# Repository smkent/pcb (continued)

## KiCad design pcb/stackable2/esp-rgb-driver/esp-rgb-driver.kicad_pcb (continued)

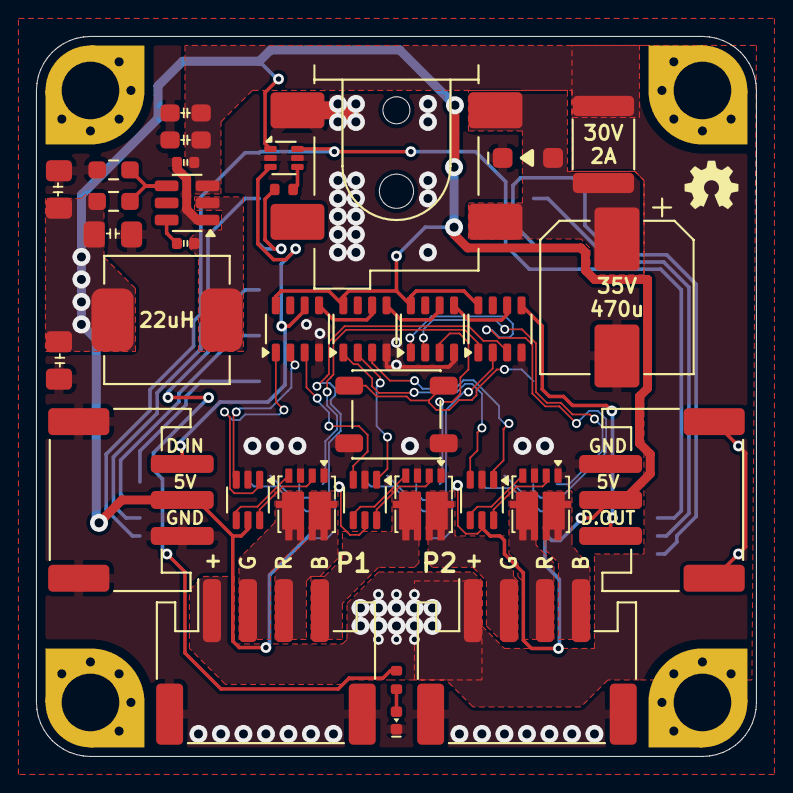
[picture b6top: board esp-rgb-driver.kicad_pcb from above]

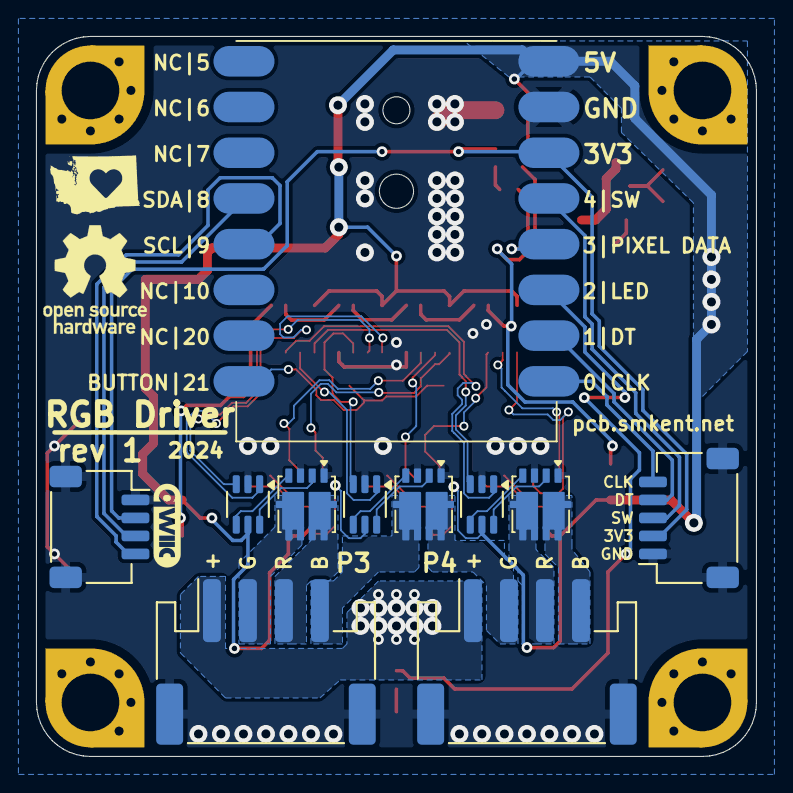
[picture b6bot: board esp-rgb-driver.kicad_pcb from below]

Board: 2 copper layers, 40.0 x 40.0 mm, 45 parts (11 on the bottom side), 59 nets.

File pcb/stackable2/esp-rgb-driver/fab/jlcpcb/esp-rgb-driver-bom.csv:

Comment,Designator,Footprint,LCSC
JST PH,"J1,J2,J3,J4",connectors:JST_PH_S4B-PH-SM4-TB_1x04-1MP_P2.00mm_Horizontal,
LED,LED1,led:LED_0402_1005Metric,
30V 2A,F1,Fuse:Fuse_1812_4532Metric,
22u,"C5,C6,C7",custom:C_0805_2012Metric_Pad1.18x1.45mm_HandSolder,
ZC010DNG,"Q1,Q2,Q3,Q4,Q5,Q6",packages:PDFN-8_L3.2-W3.1-P0.65-LS3.4-BL-EP2,C36499170
100K,R1,Resistor_SMD:R_0603_1608Metric_Pad0.98x0.95mm_HandSolder,
WS2811F,"U3,U4,U5,U6",packages:FSOP-8_L3.3-W1.7-P0.80-LS2.9-BL,C5446692
NC7WZ14,"U7,U8,U9,U10,U11,U12",packages:SOT-363_SC-70-6_HandSolder,
0u1,"C3,C4",passives:C_0402_1005Metric,
13K3,R2,Resistor_SMD:R_0603_1608Metric_Pad0.98x0.95mm_HandSolder,
~,SM1,modules:ESP32-C3-Super-Mini-Castellated-SMD-only,
Qwiic,J8,connectors:Qwiic-SMD-horizontal-logo,
TPS54202DDCR,U1,Package_TO_SOT_SMD:SOT-23-6,C191884
470u,C0,Capacitor_SMD:CP_Elec_8x10,
D_TVS,D1,packages:D_SOD-123F,
10K,R4,passives:R_0402_1005Metric,
JST SH,J7,connectors:JST_SH_SM05B-SRSS-TB_1x05-1MP_P1.00mm_Horizontal,
SN74LVC1T45DRL,U2,Package_TO_SOT_SMD:SOT-563,
10u,"C1,C2",custom:C_0603_1608Metric_Pad1.08x0.95mm_HandSolder,
22u,L1,passives:L_Power_7.0x6.6mm_0630,
SW_Push,SW1,Button_Switch_SMD:SW_SPST_PTS647_Sx50,
300R,R3,passives:R_0402_1005Metric,
STEMMA-Signal,"J5,J6",connectors:STEMMA-Signal-SMD-horizontal,
Barrel Jack,J0,custom:DC-IN_DC-050-2.0-BB_rev2,

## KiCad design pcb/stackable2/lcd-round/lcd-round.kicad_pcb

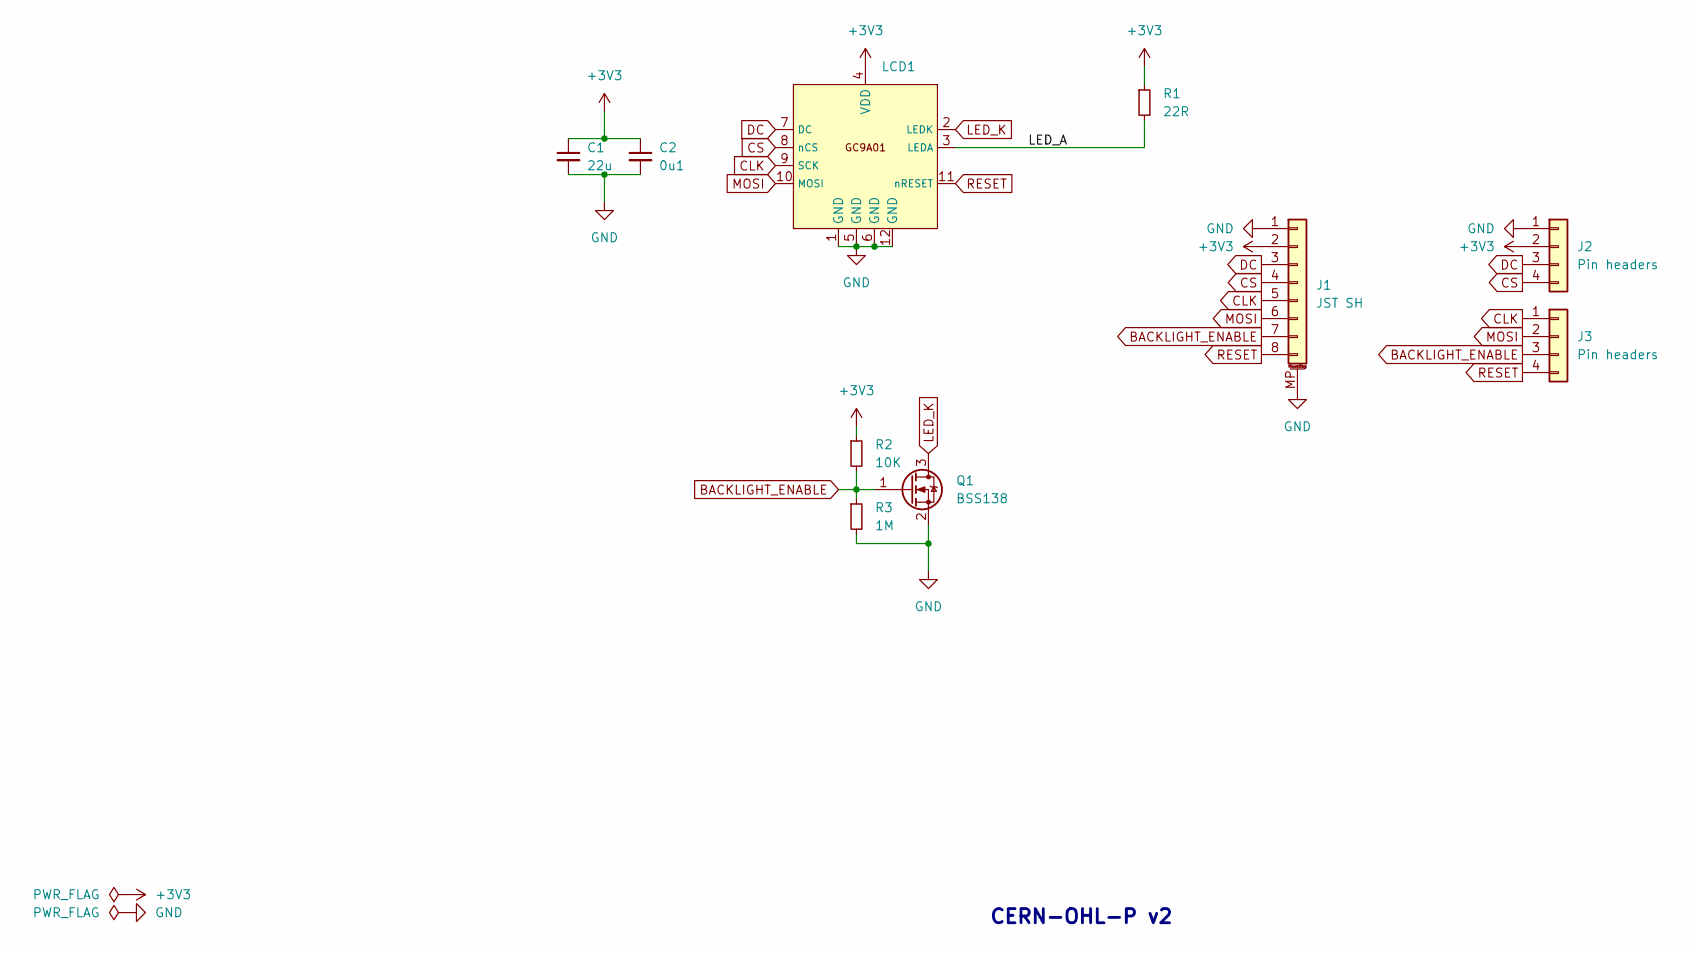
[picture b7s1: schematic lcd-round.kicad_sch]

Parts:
C1: 22u; C_0603_1608Metric_Pad1.08x0.95mm_HandSolder
C2: 0u1; C_0603_1608Metric_Pad1.08x0.95mm_HandSolder
J1: JST SH; JST_SH_SM08B-SRSS-TB_1x08-1MP_P1.00mm_Horizontal
J2: Pin headers; PinHeader_1x04_P2.54mm_Vertical_SMD_Pin1Right
J3: Pin headers; PinHeader_1x04_P2.54mm_Vertical_SMD_Pin1Left
LCD1: GC9A01; GC9A01-screen-connector-pads
Q1: BSS138; SOT-23
R1: 22R; R_0603_1608Metric_Pad0.98x0.95mm_HandSolder
R2: 10K; R_0603_1608Metric_Pad0.98x0.95mm_HandSolder
R3: 1M; R_0603_1608Metric_Pad0.98x0.95mm_HandSolder

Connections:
+3V3: C1.1, C2.1, J1.2 (+3V3), J2.2, LCD1.4 (VDD), R1.1, R2.1
/LED_A: LCD1.3 (LEDA), R1.2
BACKLIGHT_ENABLE: J1.7 (LED), J3.3, Q1.1 (G), R2.2, R3.1
CLK: J1.5 (CLK), J3.1, LCD1.9 (SCK)
CS: J1.4 (CS), J2.4, LCD1.8 (nCS)
DC: J1.3 (DC), J2.3, LCD1.7 (DC)
GND: C1.2, C2.2, J1.1 (GND), J1.MP, J2.1, LCD1.1 (GND), LCD1.5 (GND), LCD1.6 (GND), LCD1.12 (GND), Q1.2 (S), R3.2
LED_K: LCD1.2 (LEDK), Q1.3 (D)
MOSI: J1.6 (MOSI), J3.2, LCD1.10 (MOSI)
RESET: J1.8 (RST), J3.4, LCD1.11 (nRESET)

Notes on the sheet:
CERN-OHL-P v2

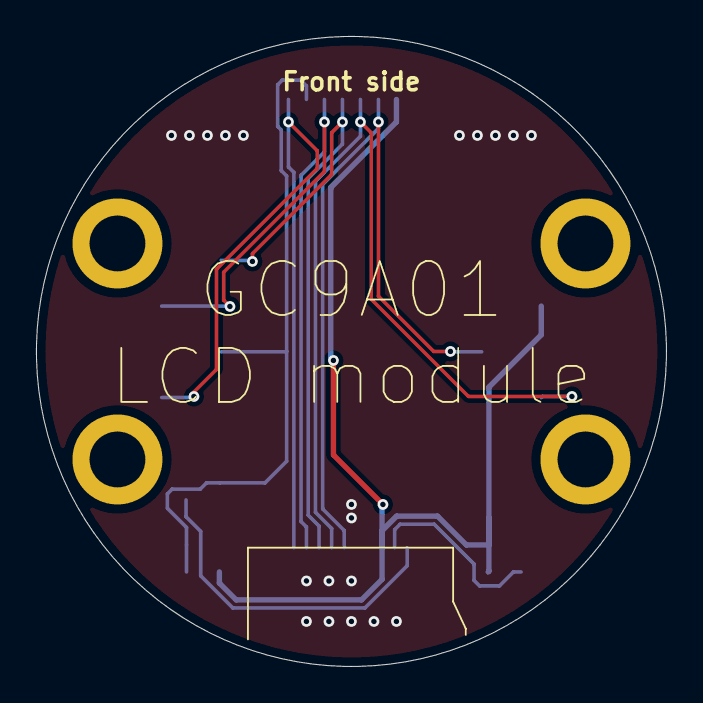
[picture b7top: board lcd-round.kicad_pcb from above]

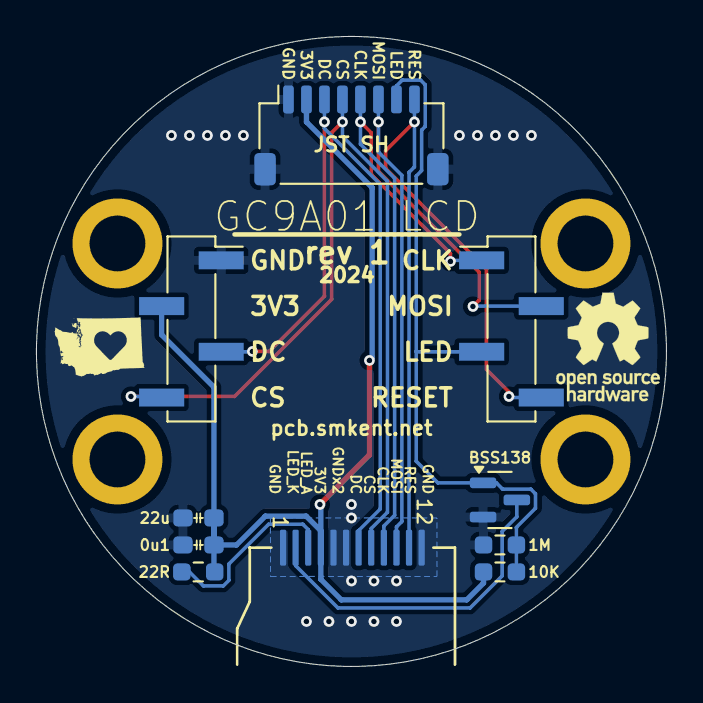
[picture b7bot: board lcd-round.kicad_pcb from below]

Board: 2 copper layers, 35.0 x 35.0 mm, 10 parts (10 on the bottom side), 10 nets.
